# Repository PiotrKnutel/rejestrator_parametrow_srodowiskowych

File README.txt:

Projekt: Rejestaror Parametrów Środowiskowych
Project: The Recorder of Environmental Parameters
Autor/Author: Piotr Knutel (piknut@linux.pl), 2020-2021

Rejestrator dokonuje pomiarów: temperatury, ciśnienia
i wilgotności względnej powietrza atmosferycznego.

Projekt oparto o mikrokontroler z rodziny STM32
(STM32F103RC), cyfrowy czujnik BME280 i kartę micro-SD.

Pomiary wykonywane są cyklicznie (co ustalony czas,
np. 5, 10, 15, 30 min) lub na żądanie użytkownika
(przez naciśnięcie przycisku). Wyniki zapisywane są
w plikach CSV, na karcie SD. Ustawienia urządzenia
wprowadza się i odczytuje poprzez opracowaną aplikację
komputerową, która komunikuje się z rejestratorem,
przez wirtualny port szeregowy i przewód USB.  

Rejestrator może być stosowane do długookresowych
badań środowisk – takich jak miejsca funkcjonowania
ludzi i maszyn, magazyny oraz kontenery towarowe
– lub jako domowa stacja pogodowa. Urządzenie może
być zasilane przewodowo lub bateryjnie. 

Projekt obejmuje:
- schemat i projekt PCB (w programie KiCAD);
- program mikroprocesora STM32F103RC (w języku C,
  w oparciu o STMCube);
- terminalową aplikację komputerową do wprowadzania
  i odczytu ustawień poprzez port szeregowy (w języku
  C#, dla Windows i Linux);
– projekt obudowy (w programie FreeCAD).

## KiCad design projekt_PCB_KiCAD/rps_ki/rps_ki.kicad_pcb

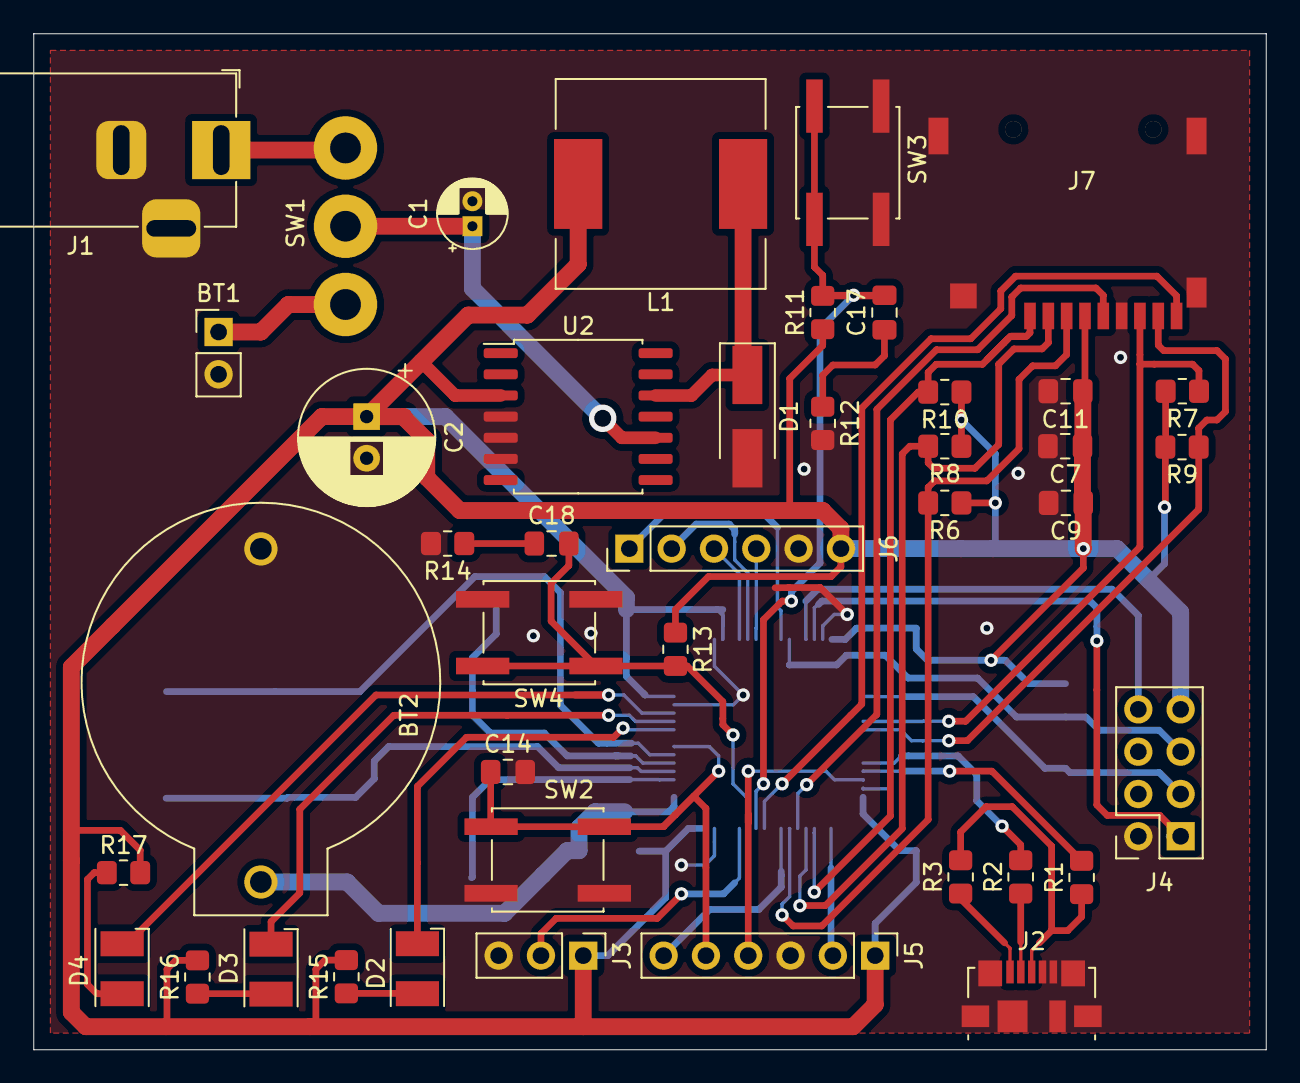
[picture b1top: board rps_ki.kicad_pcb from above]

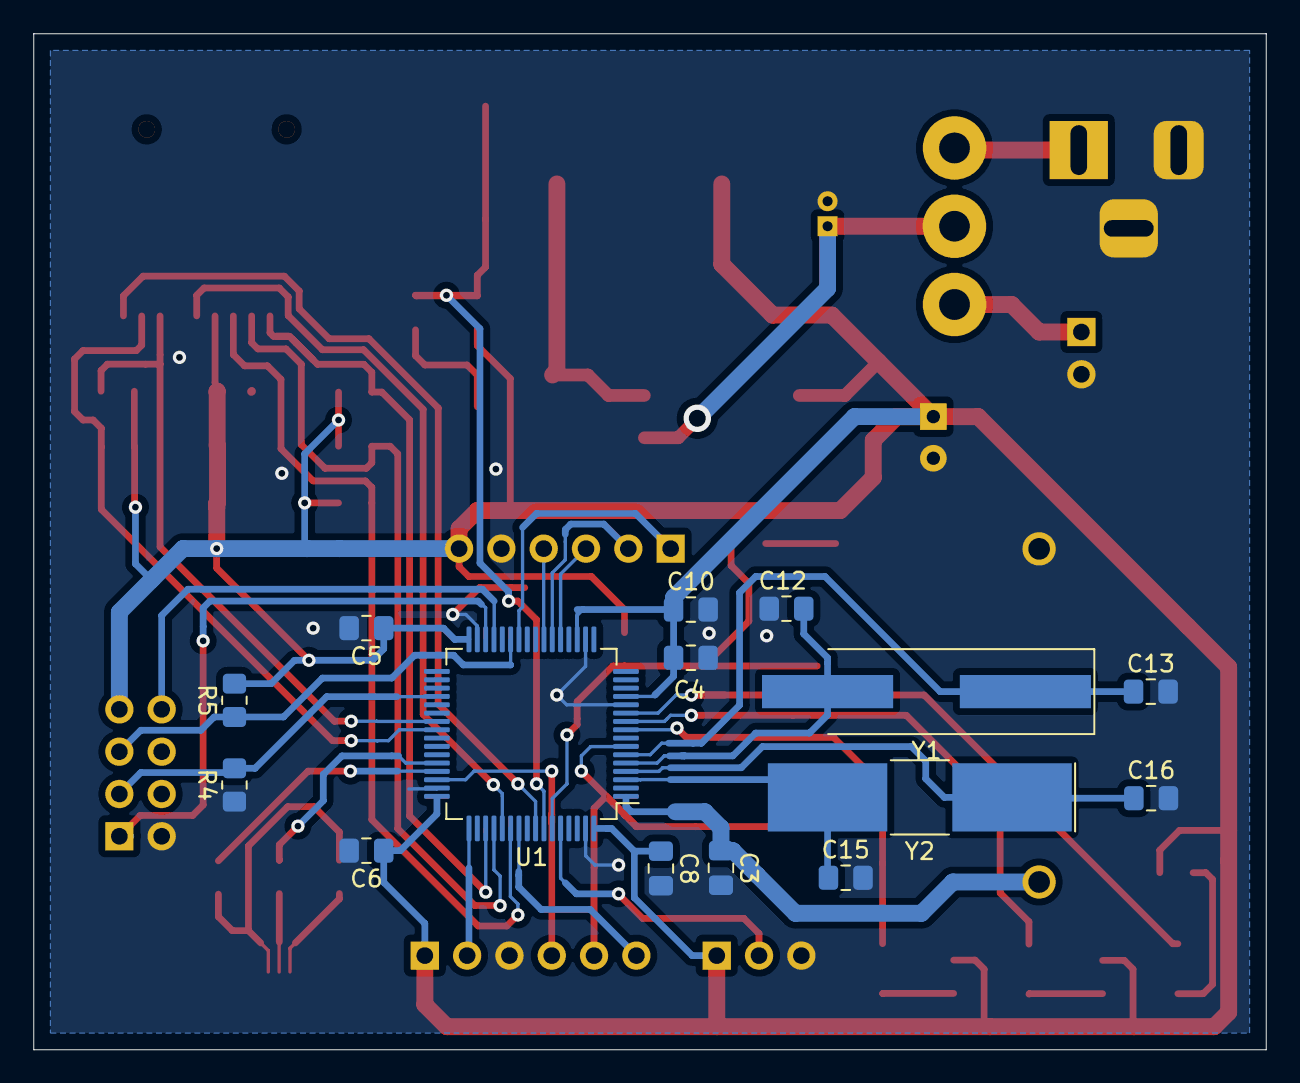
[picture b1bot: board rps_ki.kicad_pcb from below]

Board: 2 copper layers, 74.0 x 61.0 mm, 57 parts (15 on the bottom side), 46 nets.

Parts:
BT1: 6V; PinHeader_1x02_P2.54mm_Vertical
BT2: Battery_Cell; battery_holders_2032_horizontal_pk
C1: 22u; CP_Radial_D4.0mm_P1.50mm
C2: 220u; CP_Radial_D8.0mm_P2.50mm
C3, C7: 1n; C_0805_2012Metric_Pad1.18x1.45mm_HandSolder
C4, C5, C6, C8, C9, C10, C14, C17, C18: 100n; C_0805_2012Metric_Pad1.18x1.45mm_HandSolder
C11: 100u; C_0805_2012Metric_Pad1.18x1.45mm_HandSolder
C12, C13: 20p; C_0805_2012Metric_Pad1.18x1.45mm_HandSolder
C15, C16: 4,3p; C_0805_2012Metric_Pad1.18x1.45mm_HandSolder
D1: 11DQ06; D_SMA_Handsoldering
D2, D3, D4: LED; LED_PLCC-2
J1: Barrel_Jack_MountingPin; BarrelJack_Horizontal
J2: USB_B_Micro; USB_Micro-B_Molex_47346-0001
J3: Conn_01x03; PinHeader_1x03_P2.54mm_Vertical
J4: Conn_02x04_Top_Bottom; PinSocket_2x04_P2.54mm_Vertical_ESP8266-01_pk
J5, J6: Conn_01x06; PinHeader_1x06_P2.54mm_Vertical
J7: Micro_SD_Card_Det_zmodyfikowany; microSD_MCSP-Q-08-A-SG-DTE_pk
L1: 330u; L_12x12mm_H6mm
R1, R2: 20; R_0805_2012Metric_Pad1.20x1.40mm_HandSolder
R3, R11, R13: 4,7k; R_0805_2012Metric_Pad1.20x1.40mm_HandSolder
R4, R5: 10k; R_0805_2012Metric_Pad1.20x1.40mm_HandSolder
R6, R7, R8, R9, R10: 47k; R_0805_2012Metric_Pad1.20x1.40mm_HandSolder
R12, R14: 100; R_0805_2012Metric_Pad1.20x1.40mm_HandSolder
R15, R16, R17: 200; R_0805_2012Metric_Pad1.20x1.40mm_HandSolder
SW1: SW_SPDT_MSM; switch_5MS3S102AM2QE_pk
SW2, SW3, SW4: SW_Push; SW_SPST_EVQQ2
U1: STM32F103RCTx; LQFP-64_10x10mm_P0.5mm
U2: LM2574M-3.3; SOIC-14W_7.5x9mm_P1.27mm
Y1: 8MHz; Crystal_SMD_HC49-SD_HandSoldering
Y2: 32,768kHz; Crystal_SMD_SeikoEpson_MC405-2Pin_9.6x4.1mm_HandSoldering

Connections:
+3V3: C2.1, C4.1, C5.1, C6.1, C7.1, C8.1, C9.1, C10.1, C11.1, J3.1, J4.4, J5.1, J6.6, J7.4, L1.2, R5.2, R6.1, R7.2, R8.1, R9.2, R10.1, R11.1, R13.1, R15.2, R16.2, R17.2, U1.13, U1.19, U1.32, U1.48, U1.64, U2.3
/5V_DC: J1.1, SW1.3
/BAT_AA: BT1.1, SW1.1
/BAT_RTC: BT2.1, C3.1, U1.1
/BOOT0: J3.2, U1.60
/Button0: C17.2, R11.2, SW3.1, U1.58
/Button1: C18.2, R13.2, SW4.1, U1.59
/ESP_CH_PD: J4.2, R4.2, U1.36
/ESP_NRST: J4.3, R5.1, U1.27
/ESP_RX: J4.8, U1.29
/ESP_TX: J4.1, U1.30
/LED0: D2.1, U1.9
/LED1: D3.1, U1.10
/LED2: D4.1, U1.11
/NRST: C14.1, J5.5, SW2.1, U1.7
/OSC_IN: C12.1, U1.5, Y1.2
/OSC_OUT: C13.1, U1.6, Y1.1
/OSC_RTC_IN: C15.1, U1.3, Y2.2
/OSC_RTC_OUT: C16.1, U1.4, Y2.1
/SD_CD: J7.9, U1.57
/SD_CLK: J7.5, U1.53
/SD_CMD: J7.3, R6.2, U1.54
/SD_D0: J7.7, R7.1, U1.39
/SD_D1: J7.8, R9.1, U1.40
/SD_D2: J7.1, R10.2, U1.51
/SD_D3: J7.2, R8.2, U1.52
/SPI_CS: J6.1, U1.26
/SPI_MISO: J6.2, U1.22
/SPI_MOSI: J6.4, U1.23
/SPI_SCK: J6.3, U1.21
/SWCLK: J5.2, U1.49
/SWDIO: J5.4, U1.46
/SWO: J5.6, U1.55
/USB_D+: R1.2, U1.45
/USB_D-: R2.2, U1.44
/V_IN: C1.1, SW1.2, U2.10
GND: BT1.2, BT2.2, C1.2, C2.2, C3.2, C4.2, C5.2, C6.2, C7.2, C8.2, C9.2, C10.2, C11.2, C12.2, C13.2, C14.2, C15.2, C16.2, D1.2, J1.2, J1.3, J2.4, J2.5, J2.6, J3.3, J4.5, J5.3, J6.5, J7.6, J7.11, R4.1, R12.2, R14.2, SW2.2, SW3.2, SW4.2, U1.12, U1.18, U1.31, U1.47, U1.63, U2.4, U2.5, U2.6
unnamed: C17.1, R12.1
unnamed: C18.1, R14.1
unnamed: D1.1, L1.1, U2.12
unnamed: D2.2, R15.1
unnamed: D3.2, R16.1
unnamed: D4.2, R17.1
unnamed: J2.1, R3.1
unnamed: J2.2, R2.1
unnamed: J2.3, R1.1, R3.2
